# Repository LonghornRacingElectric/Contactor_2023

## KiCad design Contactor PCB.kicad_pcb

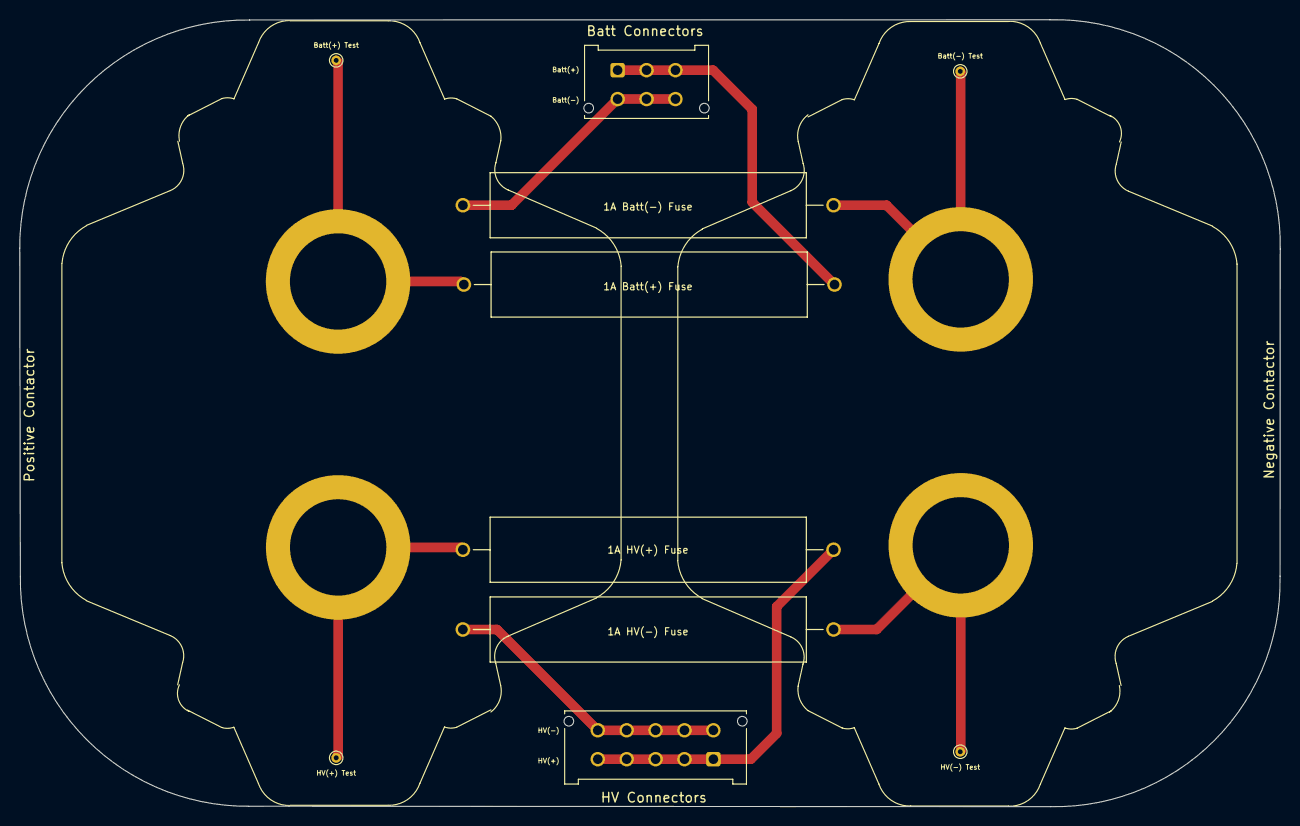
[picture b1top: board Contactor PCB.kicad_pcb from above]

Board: 2 copper layers, 130.8 x 81.7 mm, 12 parts (0 on the bottom side), 8 nets.

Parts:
F1, F2, F3, F4: 1A; 0ADAP1000RE
J1: HV Connector; Molex_Micro-Fit_3.0_43045-1012_2x05_P3.00mm_Vertical
J2: Batt Connector; Molex_Micro-Fit_3.0_43045-0612_2x03_P3.00mm_Vertical
TP1, TP5: LOAD_TEST(+); TestPoint_THTPad_D1.0mm_Drill0.5mm
TP4, TP8: LOAD_TEST(-); TestPoint_THTPad_D1.0mm_Drill0.5mm
U1, U2: Gigavac_GX21CAB; Gigavac_GX21BAB

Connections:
/Batt(+): F1.2, J2.1, J2.2, J2.3
/Batt(-): F3.2, J2.4, J2.5, J2.6
/HV(+): F2.2, J1.1, J1.2, J1.3, J1.4, J1.5
/HV(-): F4.2, J1.6, J1.7, J1.8, J1.9, J1.10
unnamed: F3.1, TP5.1, U2.2 (A2)
unnamed: F4.1, TP8.1, U2.1 (A1)
unnamed: F2.1, TP4.1, U1.2 (A2)
unnamed: F1.1, TP1.1, U1.1 (A1)

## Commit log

2022-09-26 Added 2023KicadLibrary
2022-11-28 Added layout first draft
2022-12-21 Condensed Version
2023-01-08 Finalize Board
2023-01-11 Finalized Board
